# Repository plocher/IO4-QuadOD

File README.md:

# IO4-QuadOD
## License: CERN Open Hardware Licence v1.2

IO4 Quad Detector for DCCOD and CPod detector cards

This project is a simple baseboard for current sensing detectors.
It was inspired (in reverse chronological order) by railnerd, MarkS, MRCS, RR-Cirkits and, of course, Dr Bruce Chubb.

This is a multi-purpose board - it supports 3 different use cases:

1. It can be an IO4 peripheral using the SPCoast 6-pin RJ12 connector scheme,
2. It can be hardwired using screw terminals and/or a 5VDC wallwart, or
3. With the addition of a WemosD1Mini 8266 MCU board, it can become a distributed WiFi and/or I2C peripheral. (Software TBD)

The MRCS CPod and the CMRI DCC-OD detectors both work with this baseboard.

The 2x IO4 connections are arranged so that two adjacent control
points can both monitor a shared set of detected blocks (usually
used by approach logic...).  One (master) provides a power source,
the other (slave) does not; all other signals from the IO4 connector
are in common.  This implies that both need to be connected to INPUT
configured ports.

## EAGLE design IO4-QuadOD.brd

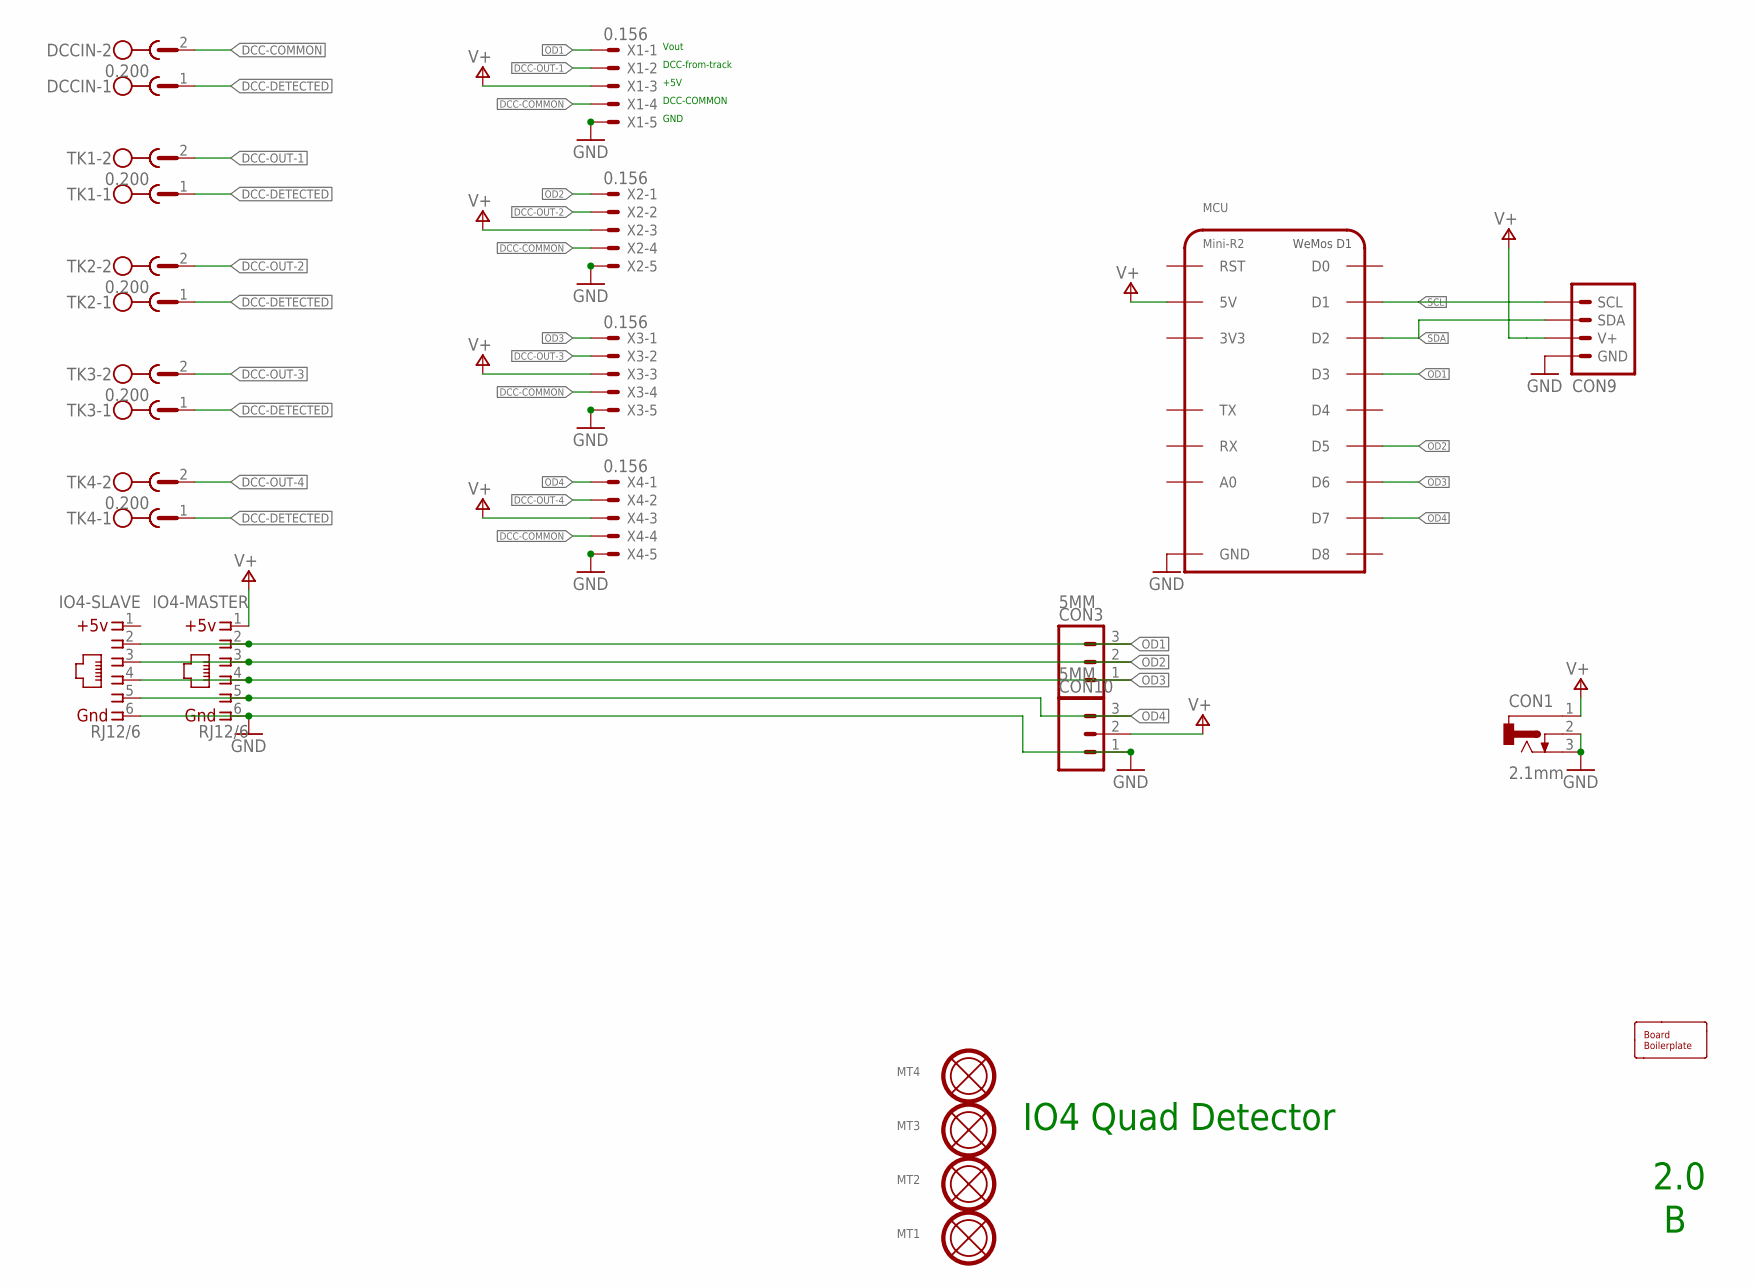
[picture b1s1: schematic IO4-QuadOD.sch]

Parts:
BOARD1: BOARD; BOARD-SEEED10X10-NOHOLES
CON1: 2.1mm; DCJ0202
CON3, CON10: 5MM; SCREWTERMINAL-5MM-3
CON9: CONNECTOR-I2CLEFT; I2C-L
DCCIN: 0.200; MSTBA2
IO4-MASTER, IO4-SLAVE: RJ12/6; RJ25-INVERTED
MCU: Mini-R2; WEMOS-D1
MT1, MT2, MT3, MT4: MOUNTINGHOLE
TK1, TK2, TK3, TK4: 0.200; MSTBA2
X1, X2, X3, X4: 0.156; KK-156-5

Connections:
1: IO4-SLAVE.1
DCC-COMMON: DCCIN.2, X1.4, X2.4, X3.4, X4.4
DCC-DETECTED: DCCIN.1, TK1.1, TK2.1, TK3.1, TK4.1
DCC-OUT-1: TK1.2, X1.2
DCC-OUT-2: TK2.2, X2.2
DCC-OUT-3: TK3.2, X3.2
DCC-OUT-4: TK4.2, X4.2
GND: CON1.2, CON1.3, CON9.GND, CON9.GND@1 (GND), CON10.1, IO4-MASTER.6, IO4-SLAVE.6, MCU.GND, X1.5, X2.5, X3.5, X4.5
OD1: CON3.3, IO4-MASTER.2, IO4-SLAVE.2, MCU.D3, X1.1
OD2: CON3.2, IO4-MASTER.3, IO4-SLAVE.3, MCU.D5, X2.1
OD3: CON3.1, IO4-MASTER.4, IO4-SLAVE.4, MCU.D6, X3.1
OD4: CON10.3, IO4-MASTER.5, IO4-SLAVE.5, MCU.D7, X4.1
SCL: CON9.SCL, CON9.SCL@1 (SCL), MCU.D1
SDA: CON9.SDA, CON9.SDA@1 (SDA), MCU.D2
V+: CON1.1, CON9.V+, CON9.V+@1 (V+), CON10.2, IO4-MASTER.1, MCU.5V, X1.3, X2.3, X3.3, X4.3

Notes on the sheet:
IO4 Quad Detector
2.0
Vout
DCC-from-track
+5V
DCC-COMMON
GND

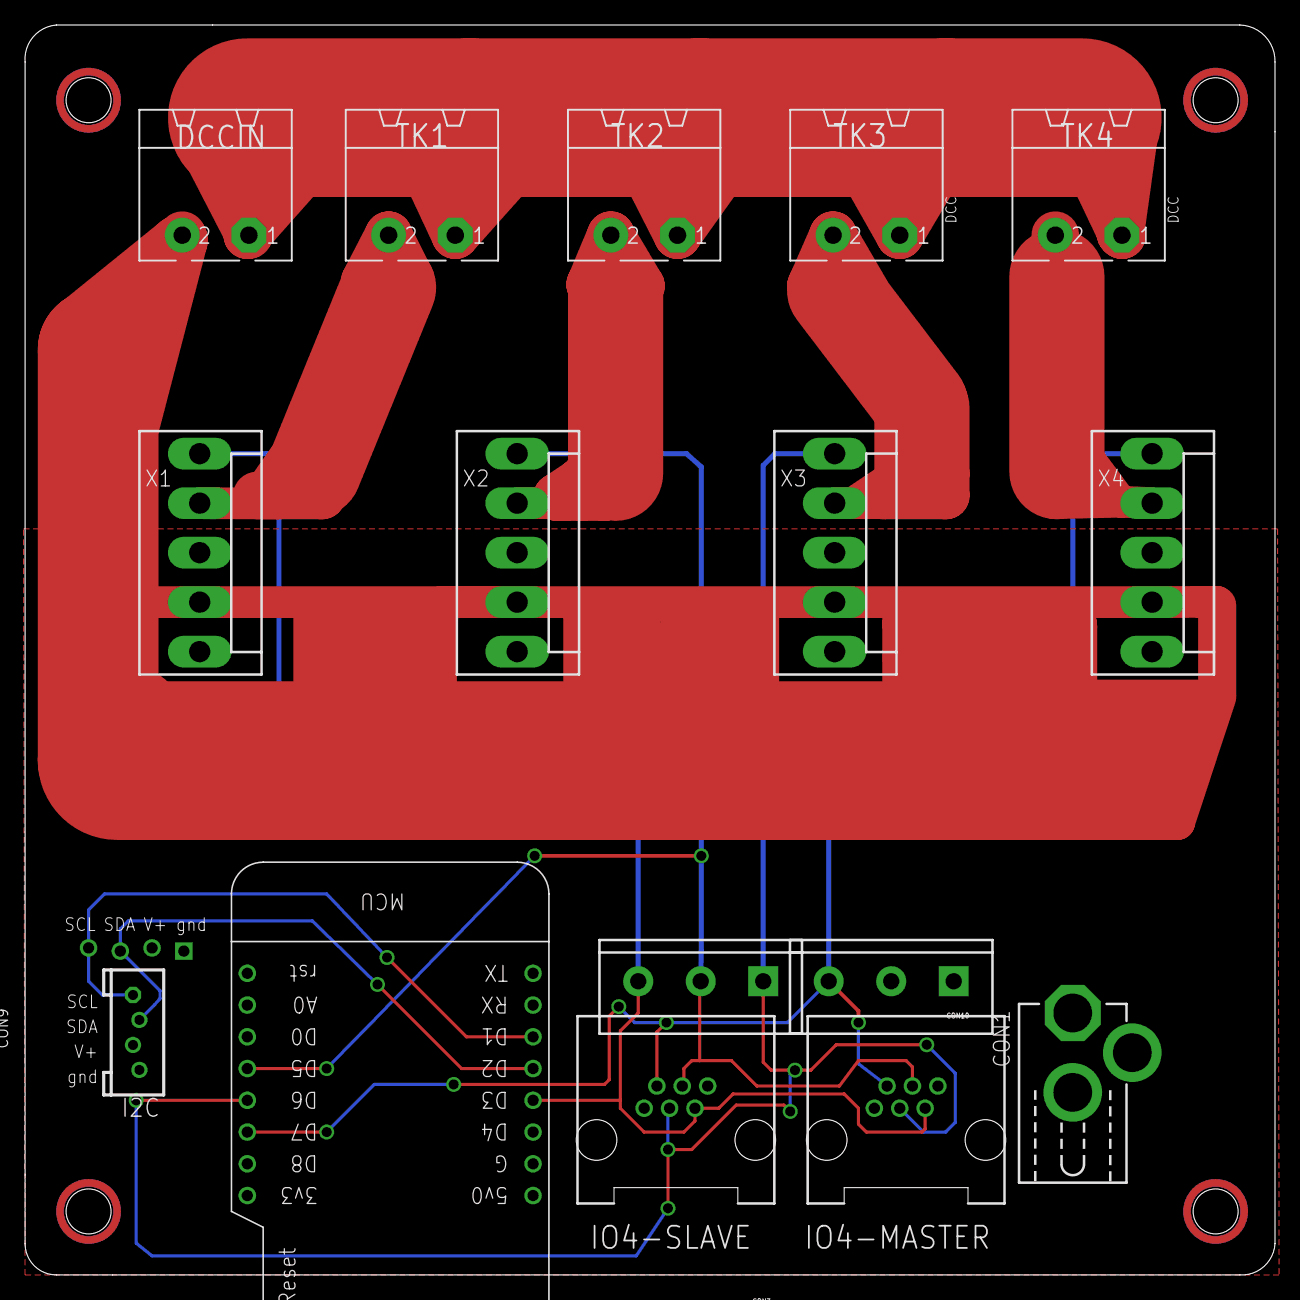
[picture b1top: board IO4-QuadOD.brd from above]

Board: 2 copper layers, 100.0 x 100.0 mm, 21 parts (0 on the bottom side), 14 nets.

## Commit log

2019-12-08 added graphic
2020-05-04 updated tags
2020-10-05 added values for connectors
2020-10-06 normalized values
